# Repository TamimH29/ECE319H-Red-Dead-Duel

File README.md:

# Red-Dead-Duel

Here is a video demo of the game:
https://www.youtube.com/watch?v=911-FPZZQl8

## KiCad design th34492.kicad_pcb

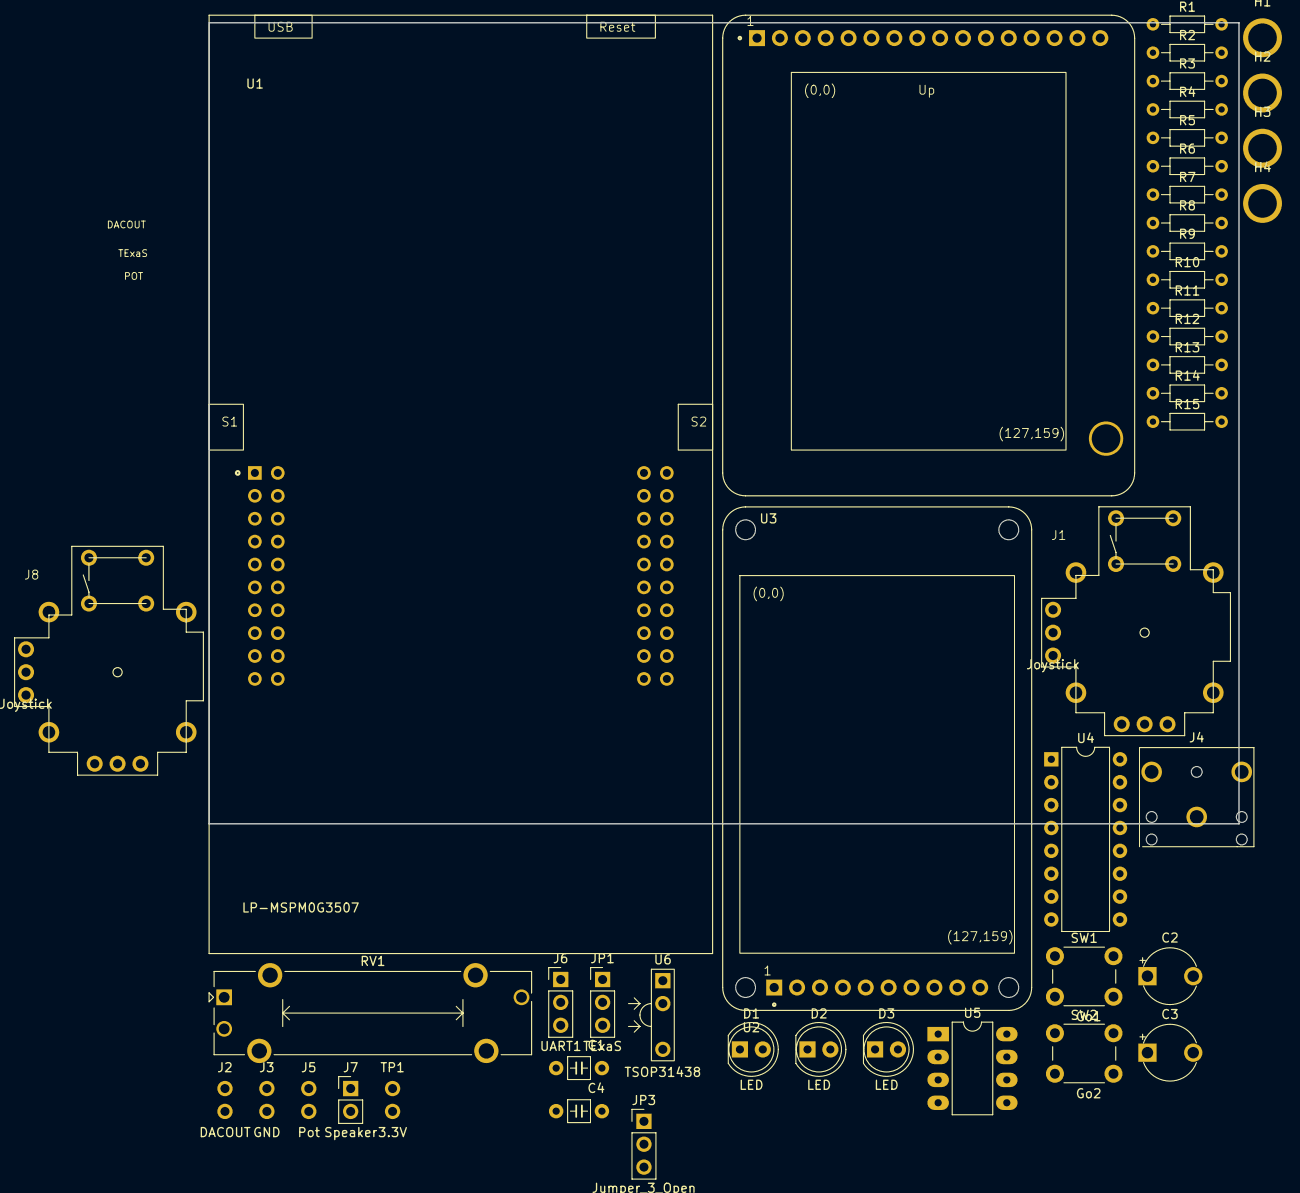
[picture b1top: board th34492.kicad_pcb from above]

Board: 2 copper layers, 114.3 x 88.9 mm, 46 parts (0 on the bottom side), 40 nets, no tracks yet.

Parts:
C1, C4: 0.1uF; C_Axial_200mil
C2: 1uF; CP_Radial_Tantal200mil
C3: 4.7uF; CP_Radial_Tantal200mil
D1, D2, D3: LED; LED_D5.0mm
H1, H2, H3, H4: MountingHole_4_40
J1, J8: Joystick; SparkfunJoystick
J2: DACOUT; Testpoint_1x02_P2.54mm
J3: GND; Testpoint_1x02_P2.54mm
J4: AudioJack; Jack_3.5mm_CUI_SJ1-3523N_Horizontal
J5: Pot; Testpoint_1x02_P2.54mm
J6: UART1; PinHeader_1x03_P2.54mm_Vertical
J7: Speaker; PinHeader_1x02_P2.54mm_Vertical
JP1: TExaS; PinHeader_1x03_P2.54mm_Vertical
JP3: Jumper_3_Open; PinHeader_1x03_P2.54mm_Vertical
R1, R3, R14: 10k; R_Axial_DIN0204_L3.6mm_D1.6mm_P7.62mm_Horizontal
R2, R4: 470; R_Axial_DIN0204_L3.6mm_D1.6mm_P7.62mm_Horizontal
R5, R6, R7, R8, R12: 1.5k; R_Axial_DIN0204_L3.6mm_D1.6mm_P7.62mm_Horizontal
R9, R10, R11: 12k; R_Axial_DIN0204_L3.6mm_D1.6mm_P7.62mm_Horizontal
R13: 20k; R_Axial_DIN0204_L3.6mm_D1.6mm_P7.62mm_Horizontal
R15: 220; R_Axial_DIN0204_L3.6mm_D1.6mm_P7.62mm_Horizontal
RV1: PTA2043; PTA2043pot
SW1: Go1; SW_PUSH_6mm
SW2: Go2; SW_PUSH_6mm
TP1: 3.3V; Testpoint_1x02_P2.54mm
U1: LP-MSPM0G3507; ti_LP_MSPM0G3507
U2: Adafruit ST7735R; adafruit_st7735r
U3: HiLetGo_ST7735R; hiletgo_st7735r
U4: ULN2003B; DIP-16_W7.62mm
U5: MCP34119P; DIP-8_W7.62mm_LongPads
U6: TSOP31438

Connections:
+3V3: C4.1, J1.3 (V+), J1.4 (H+), J1.12 (SEL+), J8.3 (V+), J8.4 (H+), J8.12 (SEL+), RV1.3, SW1.2, SW2.2, TP1.1 (A), TP1.2 (B), U1.J1_1 (+3.3V), U2.2 (VCC), U2.10 (LITE), U3.2 (VCC), U3.15 (LED+), U6.2 (Vs)
+5V: R15.1, U1.J3_1 (+VBUS), U4.9 (COM), U5.6 (Vcc)
DACOUT: J2.1 (A), J2.2 (B), J4.R (ring), J4.T (tip), JP3.1 (A), R5.1, R6.1, R8.1, R9.1, R10.1, R11.1, R12.1
GND: C2.2, C3.2, C4.2, D1.1 (K), D2.1 (K), J1.1 (V-), J1.6 (H-), J3.1 (A), J3.2 (B), J4.S (sleeve), J6.1 (A), J8.1 (V-), J8.6 (H-), R1.2, R3.2, RV1.1, U1.J2_1 (GND), U1.J3_2 (GND), U2.1 (GND), U3.1 (GND), U3.16 (LED-), U4.2 (2B), U4.3 (3B), U4.4 (4B), U4.5 (5B), U4.6 (6B), U4.7 (7B), U4.8 (E), U5.1 (CD), U5.7 (GND), U6.1 (Gnd)
unnamed: C1.2, R13.2
unnamed: D1.2 (A), R2.2
unnamed: D2.2 (A), R4.2
unnamed: D3.2 (A), R15.2
unnamed: D3.1 (K), U4.16 (1C)
unnamed: C1.1, JP1.1 (A), JP3.2 (C)
unnamed: R7.1, R12.2
unnamed: C2.1, U5.3 (FC1)
unnamed: C3.1, U5.2 (FC2)
unnamed: R13.1, R14.2, U5.4 (VIN)
unnamed: J7.1, R14.1, U5.5 (VO1)
unnamed: J7.2, U5.8 (VO2)
PA8: J6.2 (B), U1.J1_4 (PA8), U4.1 (1B)
PA12: U1.J4_9 (PA12), U2.5 (CARD_CS), U3.14 (SDC_CS)
PA13: U1.J4_10 (PA13), U2.4 (D/C), U3.7 (TFTDC)
PA15: JP3.3 (B), U1.J3_10 (PA15)
PA16: R2.1, R3.1, SW2.1, U1.J3_9 (PA16)
PA17: R1.1, R4.1, SW1.1, U1.J3_8 (PA17)
PA22: J6.3 (C), U1.J3_4 (PA22), U6.3 (Out)
PA24: J8.11 (SEL-), U1.J3_7 (PA24)
PA25: J1.11 (SEL-), U1.J1_2 (PA25)
PA26: J1.5 (Hori), U1.J1_5 (PA26)
PA27: J1.2 (Vert), U1.J1_8 (PA27)
PB0: R11.2, U1.J2_9 (PB0)
PB1: R9.2, R10.2, U1.J4_2 (PB1)
PB2: R7.2, U1.J1_9 (PB2)
PB3: R8.2, U1.J1_10 (PB3)
PB4: R5.2, R6.2, U1.J4_1 (PB4)
PB6: U1.J2_8 (PB6), U2.6 (TFT_CS), U3.10 (TFT_CS)
PB7: U1.J2_7 (PB7), U2.9 (MISO), U3.12 (SDC_MISO)
PB8: U1.J2_6 (PB8), U2.7 (MOSI), U3.8 (TFTMOSI), U3.13 (SDC_MOSI)
PB9: U1.J1_7 (PB9), U2.8 (SCK), U3.9 (TFTSCK), U3.11 (SDCSCK)
PB15: U1.J2_4 (PB15), U2.3 (RESET), U3.6 (RESET)
PB18: J5.1 (A), J5.2 (B), JP1.3 (B), RV1.2, U1.J3_5 (PB18)
PB20: J8.2 (Vert), JP1.2 (C), U1.J4_5 (PB20)
PB24: J8.5 (Hori), U1.J1_6 (PB24)

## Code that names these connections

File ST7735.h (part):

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<tr><th>Pin <th>Connection <th>Description
<tr><td>10<td>+3.3<td>Backlight   
<tr><td>9 <td>nc  <td>SPI1 MISO (used for SDC)     
<tr><td>8 <td>PB9 <td>SPI1 SCLK clock out
<tr><td>7 <td>PB8 <td>SPI1 PICO data out    
<tr><td>6 <td>PB6 <td>SPI1 CS0=TFT_CS   
<tr><td>5 <td>nc  <td>CARD_CS (used for SDC)   
<tr><td>4 <td>PA13<td>Data/Command(GPIO), high for data, low for command   
<tr><td>3 <td>PB15<td>RESET, low to reset,  (GPIO)   
<tr><td>2 <td>+3.3<td>VCC   
<tr><td>1 <td>Gnd <td>ground   
</table>
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<tr><th>Pin<th>Connection
<tr><td>VCC  <td> +3.3 V
<tr><td>GND  <td> Ground
<tr><td>!SCL <td> SPI1 SCLK: PB9 clock
<tr><td>!SDA <td> SPI1 PICO: PB8 MOSI SPI data from microcontroller to TFT or SDC
<tr><td>DC   <td> GPIO       PA13 TFT data/command
<tr><td>RES  <td> GPIO       PB15 TFT reset
<tr><td>CS   <td> SPI1 CS0:  PB6 TFT_CS, active low to enable TFT
<tr><td>*CS  <td> (NC) SDC_CS, active low to enable SDC
<tr><td>MISO <td> (NC) MISO SPI data from SDC to microcontroller
<tr><td>SDA  <td> (NC) I2C data for ADXL345 accelerometer
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<tr><th>Pin<th>Connection
<tr><td>VCC  <td> +3.3 V
<tr><td>GND  <td> Ground
/<tr><td>!SCL<td> SPI1 SCLK: PB9
<tr><td>!SDA <td> SPI1 PICO: PB8 MOSI SPI data from microcontroller to TFT or SDC
<tr><td>DC   <td> GPIO       PA13 TFT data/command
<tr><td>RES  <td> GPIO       PB15 TFT reset
<tr><td>CS   <td> SPI1 CS0:  PB6 TFT_CS, active low to enable TFT
<tr><td>*CS  <td> (NC) SDC_CS, active low to enable SDC
<tr><td>MISO <td> (NC) MISO SPI data from SDC to microcontroller
<tr><td>X<td> (NC) analog input X-axis from ADXL335 accelerometer
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<tr><td>MOSI   <td>13<td>SDC, to MOSI
<tr><td>MISO   <td>12<td>SDC, to MISO
<tr><td>SCK    <td>11<td>SDC, to serial clock
<tr><td>CS     <td>10<td>TFT, to PB6  SPI1 CS0
<tr><td>SCL    <td> 9<td>TFT, to PB9  SPI1 SCLK
<tr><td>SDA    <td> 8<td>TFT, to PB8  MOSI SPI1 PICO
<tr><td>A0     <td> 7<td>TFT, to PA13 Data/Command, high for data, low for command
<tr><td>RESET  <td> 6<td>TFT, to PB15 reset (GPIO), low to reset
<tr><td>NC     <td>3,4,5<td>not connected
<tr><td>VCC    <td> 2<td>to +3.3 V
<tr><td>GND    <td> 1<td>to ground
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<caption id="Tyenazapins">Tyenaza Tyenazaqhf72mi9s3 pins </caption>
<tr><th>signal<th>Pin<th>Connection
<tr><td>LED <td>8<td> to +3.3 V
<tr><td>SCK <td>7<td>SCLK         to PB9 SPI1 SCLK
<tr><td>SDA <td>6<td>MOSI,        to PB8 SPI1 PICO
<tr><td>A0  <td>5<td>Data/Command to PA13 (GPIO), high for data, low for command
<tr><td>RESET <td>4<td>to PB15 (GPIO), low to reset
<tr><td>CS  <td>3<td>to PB6 SPI1 CS0:
<tr><td>Gnd <td>2<td>to ground
<tr><td>VCC <td>1<td>to +3.3 V
</table>
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<tr><th>Pin <th>Connection <th>Description
<tr><td>10<td>+3.3<td>Backlight   
<tr><td>9 <td>nc  <td>SPI1 MISO (used for SDC)     
<tr><td>8 <td>PB9 <td>SPI1 SCLK clock out
<tr><td>7 <td>PB8 <td>SPI1 PICO data out    
<tr><td>6 <td>PB6 <td>SPI1 CS0=TFT_CS   
<tr><td>5 <td>nc  <td>CARD_CS (used for SDC)   
<tr><td>4 <td>PA13<td>Data/Command(GPIO), high for data, low for command   
<tr><td>3 <td>PB15<td>RESET, low to reset,  (GPIO)   
<tr><td>2 <td>+3.3<td>VCC   
<tr><td>1 <td>Gnd <td>ground   
</table>
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<tr><th>Pin<th>Connection
<tr><td>VCC  <td> +3.3 V
<tr><td>GND  <td> Ground
<tr><td>!SCL <td> SPI1 SCLK: PB9 clock
<tr><td>!SDA <td> SPI1 PICO: PB8 MOSI SPI data from microcontroller to TFT or SDC
<tr><td>DC   <td> GPIO       PA13 TFT data/command
<tr><td>RES  <td> GPIO       PB15 TFT reset
<tr><td>CS   <td> SPI1 CS0:  PB6 TFT_CS, active low to enable TFT
<tr><td>*CS  <td> (NC) SDC_CS, active low to enable SDC
<tr><td>MISO <td> (NC) MISO SPI data from SDC to microcontroller
<tr><td>SDA  <td> (NC) I2C data for ADXL345 accelerometer
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<tr><th>Pin<th>Connection
<tr><td>VCC  <td> +3.3 V
<tr><td>GND  <td> Ground
/<tr><td>!SCL<td> SPI1 SCLK: PB9
<tr><td>!SDA <td> SPI1 PICO: PB8 MOSI SPI data from microcontroller to TFT or SDC
<tr><td>DC   <td> GPIO       PA13 TFT data/command
<tr><td>RES  <td> GPIO       PB15 TFT reset
<tr><td>CS   <td> SPI1 CS0:  PB6 TFT_CS, active low to enable TFT
<tr><td>*CS  <td> (NC) SDC_CS, active low to enable SDC
<tr><td>MISO <td> (NC) MISO SPI data from SDC to microcontroller
<tr><td>X<td> (NC) analog input X-axis from ADXL335 accelerometer
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<tr><td>MOSI   <td>13<td>SDC, to MOSI
<tr><td>MISO   <td>12<td>SDC, to MISO
<tr><td>SCK    <td>11<td>SDC, to serial clock
<tr><td>CS     <td>10<td>TFT, to PB6  SPI1 CS0
<tr><td>SCL    <td> 9<td>TFT, to PB9  SPI1 SCLK
<tr><td>SDA    <td> 8<td>TFT, to PB8  MOSI SPI1 PICO
<tr><td>A0     <td> 7<td>TFT, to PA13 Data/Command, high for data, low for command
<tr><td>RESET  <td> 6<td>TFT, to PB15 reset (GPIO), low to reset
<tr><td>NC     <td>3,4,5<td>not connected
<tr><td>VCC    <td> 2<td>to +3.3 V
<tr><td>GND    <td> 1<td>to ground
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<caption id="Tyenazapins2">Tyenaza Tyenazaqhf72mi9s3 pins </caption>
<tr><th>signal<th>Pin<th>Connection
<tr><td>LED <td>8<td> to +3.3 V
<tr><td>SCK <td>7<td>SCLK         to PB9 SPI1 SCLK
<tr><td>SDA <td>6<td>MOSI,        to PB8 SPI1 PICO
<tr><td>A0  <td>5<td>Data/Command to PA13 (GPIO), high for data, low for command
<tr><td>RESET <td>4<td>to PB15 (GPIO), low to reset
<tr><td>CS  <td>3<td>to PB6 SPI1 CS0:
<tr><td>Gnd <td>2<td>to ground
<tr><td>VCC <td>1<td>to +3.3 V
</table>
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
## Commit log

2024-07-19 Updated video demo

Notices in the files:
ST7735.h:
MIT license, all text above must be included in any redistribution
@copyright Copyright 2023 by Jonathan W. Valvano, valvano@mail.utexas.edu,
@warning AS-IS
